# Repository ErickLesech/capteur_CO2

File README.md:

# capteur_CO2

Projet Capteur C02

- Page html
- Projet PCB
- Code arduino

Kahina AIT OUFELLA
Erick LE SECH

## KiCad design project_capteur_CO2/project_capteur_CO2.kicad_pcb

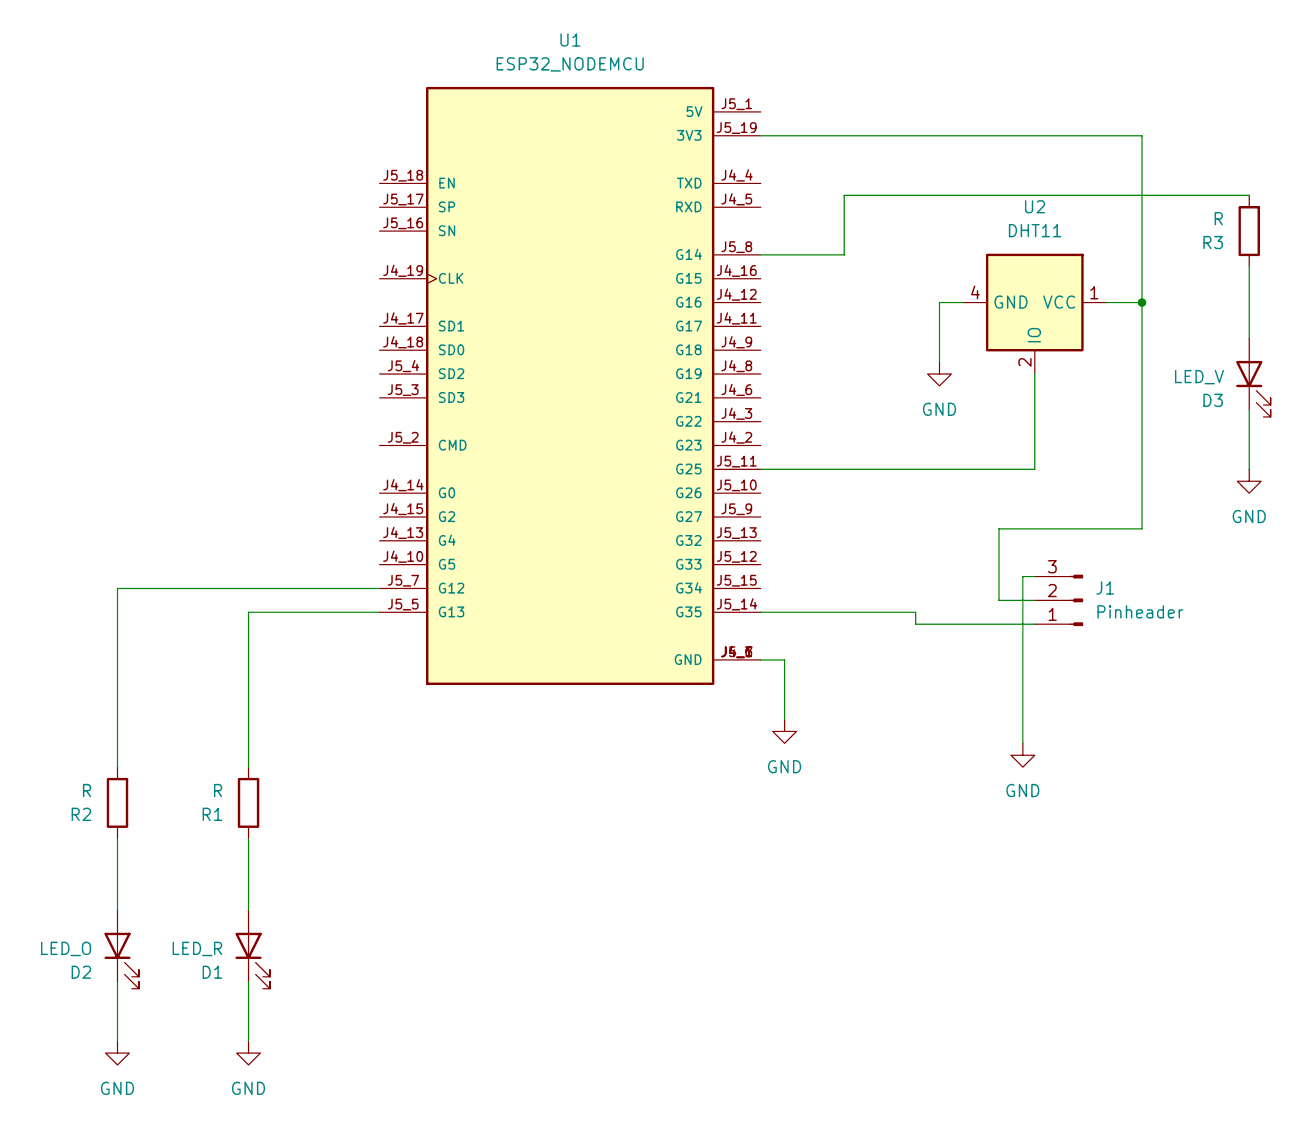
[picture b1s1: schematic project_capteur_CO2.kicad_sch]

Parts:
D1: LED_R; LED_D3.0mm
D2: LED_O; LED_D3.0mm
D3: LED_V; LED_D3.0mm
J1: Pinheader; PinHeader_1x03_P1.00mm_Vertical
R1, R2, R3: R; R_Axial_DIN0309_L9.0mm_D3.2mm_P12.70mm_Horizontal
U1: ESP32_NODEMCU; MODULE_ESP32_NODEMCU
U2: DHT11; Aosong_DHT11_5.5x12.0_P2.54mm

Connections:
GND: D1.1 (K), D2.1 (K), D3.1 (K), J1.3, U1.J4_1 (GND), U1.J4_7 (GND), U1.J5_6 (GND), U2.4 (GND)
unnamed: D1.2 (A), R1.1
unnamed: D2.2 (A), R2.1
unnamed: D3.2 (A), R3.1
unnamed: J1.1, U1.J5_14 (G35)
unnamed: J1.2, U1.J5_19 (3V3), U2.1 (VCC)
unnamed: R1.2, U1.J5_5 (G13)
unnamed: R2.2, U1.J5_7 (G12)
unnamed: R3.2, U1.J5_8 (G14)
unnamed: U1.J5_11 (G25), U2.2 (IO)

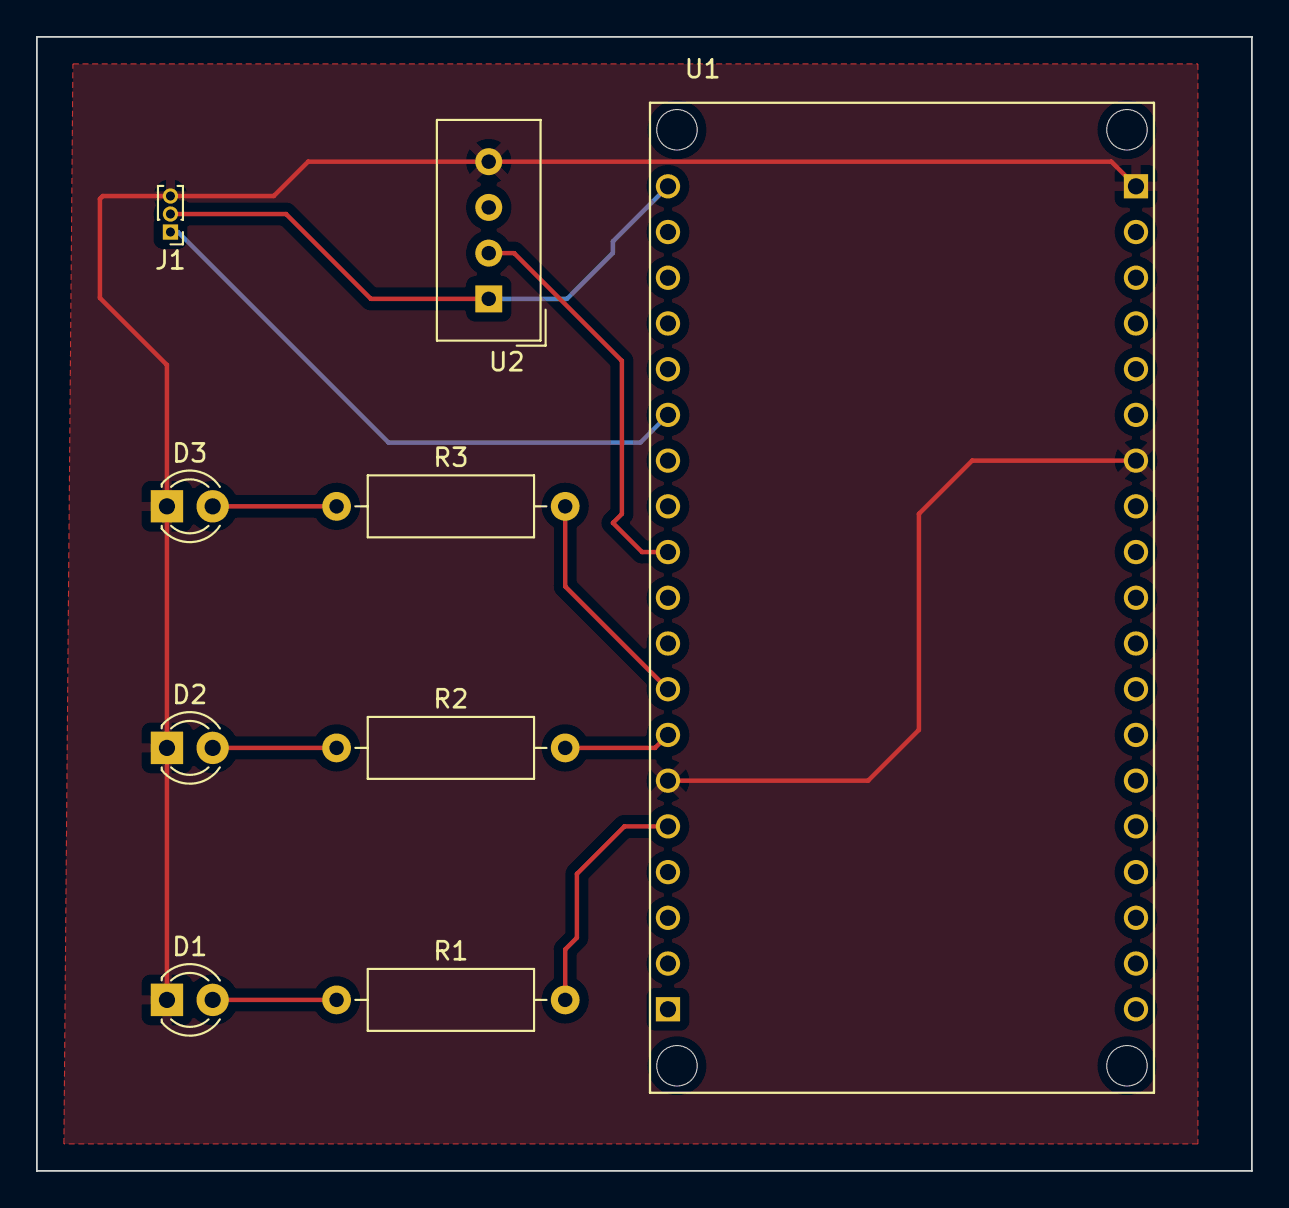
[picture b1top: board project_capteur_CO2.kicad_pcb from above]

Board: 2 copper layers, 67.5 x 63.0 mm, 9 parts (0 on the bottom side), 10 nets.

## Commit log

2022-10-24 Projet PCB
2022-10-25 ajout de noms
2022-10-25 ajout de la communication avec la BDD et affichage sur graphe
2022-10-26 ajout couleur dans le graphe
2022-10-26 chart with gradient color
2022-10-28 schéma et empreinte fait mais empreinte capteur à refaire
2022-10-28 gantt projet
2022-10-28 ajout planning 3eme semaine
2022-11-02 pinheader - coorection led empreinte ajouter
2022-11-02 ajout graphe temperature et humidité
2022-11-02 canve inline
2022-11-02 canva inline
2022-11-02 style css
2022-11-03 planning des 8 semaines
2022-11-03 animation slide
2022-11-03 css animation
2022-11-04 mise à jour planning semaine 4
2022-11-04 add carousel from bootstrap
2022-11-07 ajout bandeau jaune UBO & texte en blanc
2022-11-07 image pour la page web
2022-11-07 enlever bout de code js
2022-11-07 ajout tache des semaines suivantes
2022-11-09 modification planning semaine 4 & 5
2022-11-09 ajout texte
2022-11-09 modification css
